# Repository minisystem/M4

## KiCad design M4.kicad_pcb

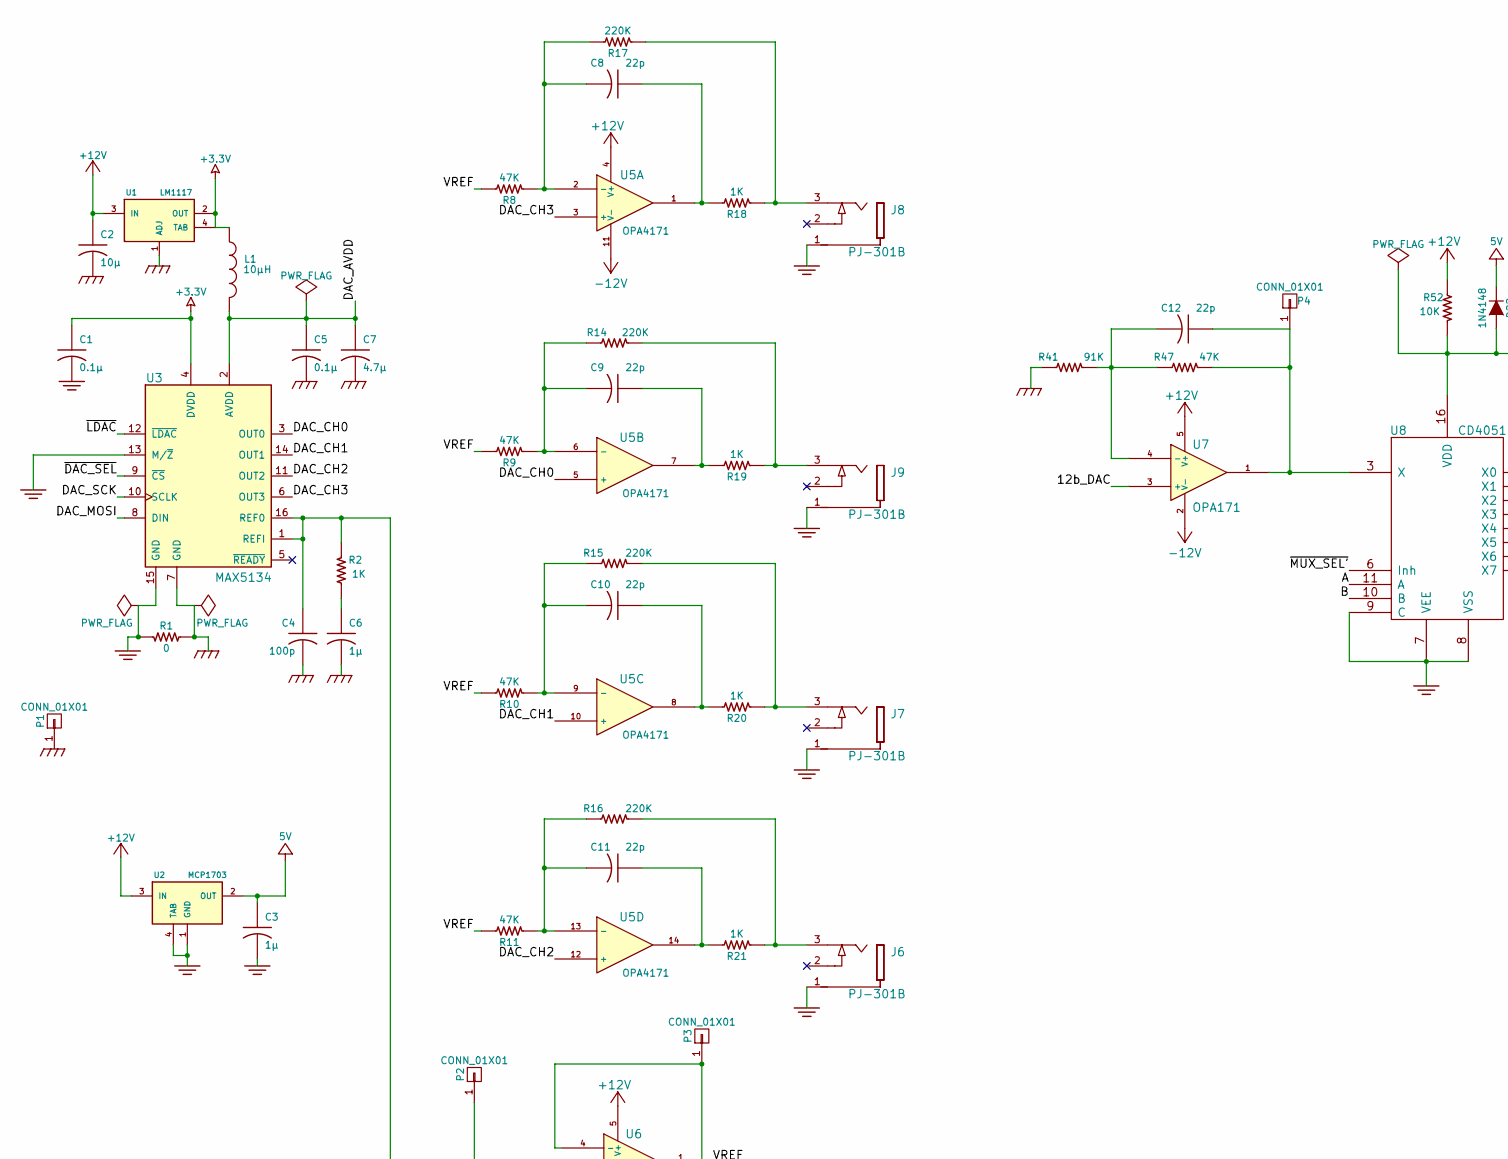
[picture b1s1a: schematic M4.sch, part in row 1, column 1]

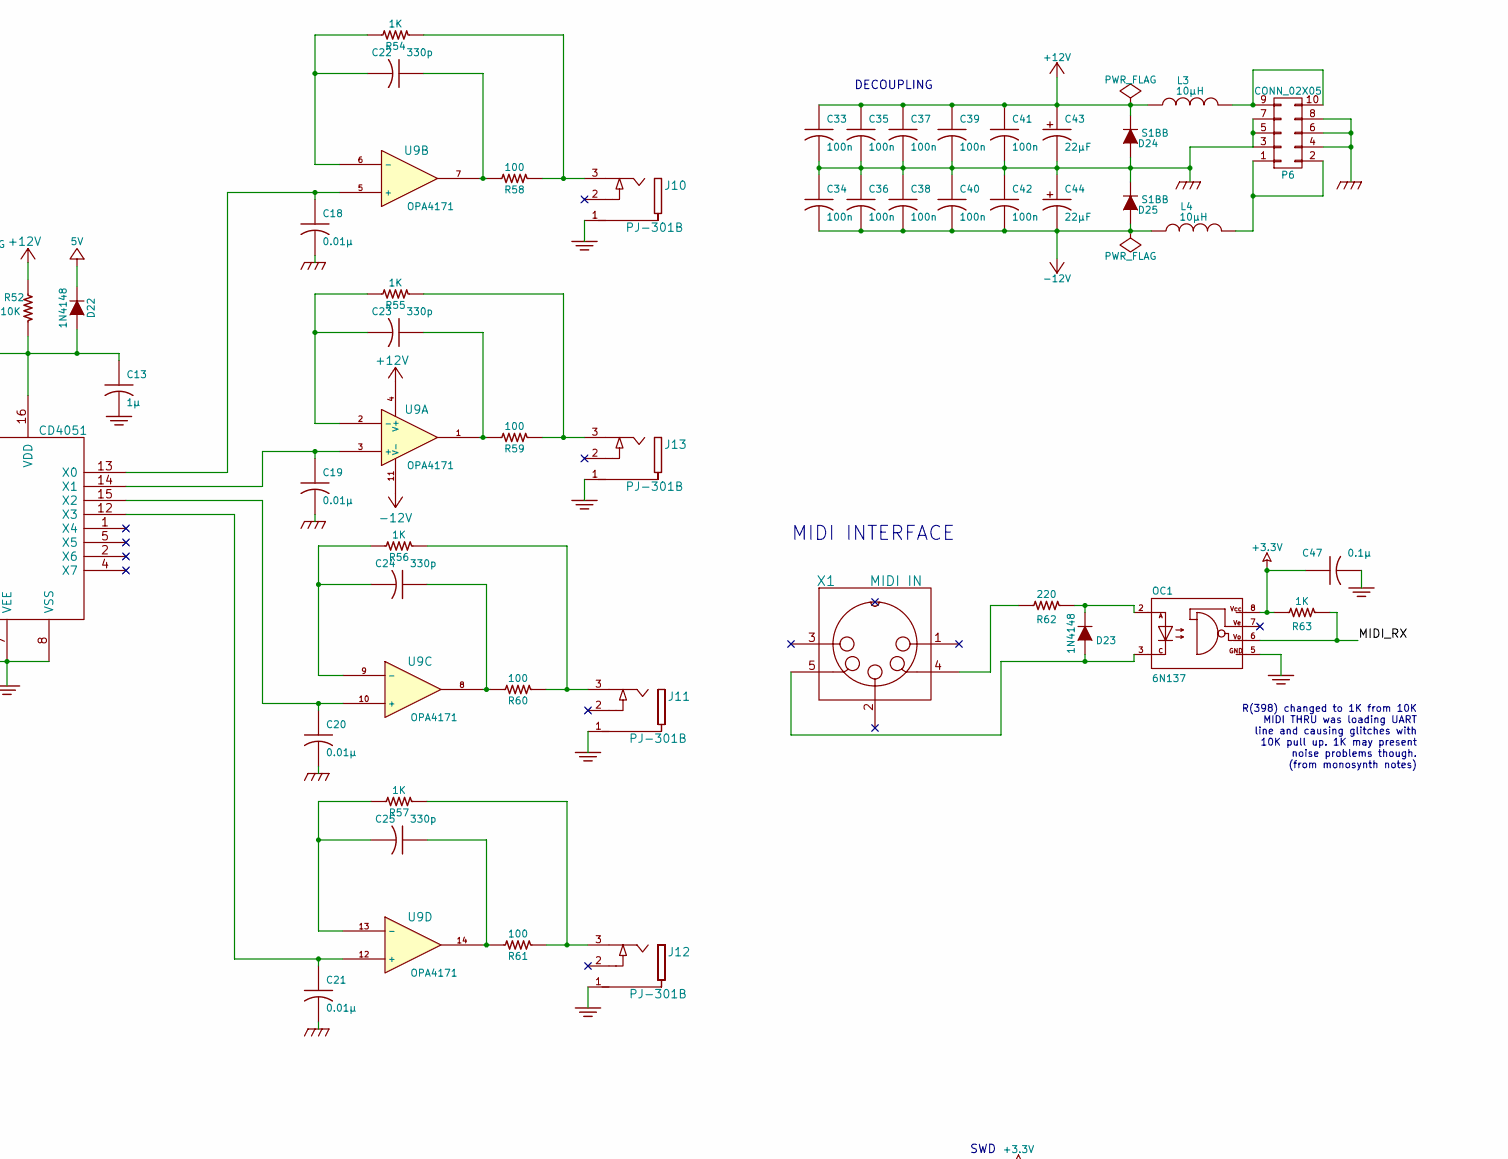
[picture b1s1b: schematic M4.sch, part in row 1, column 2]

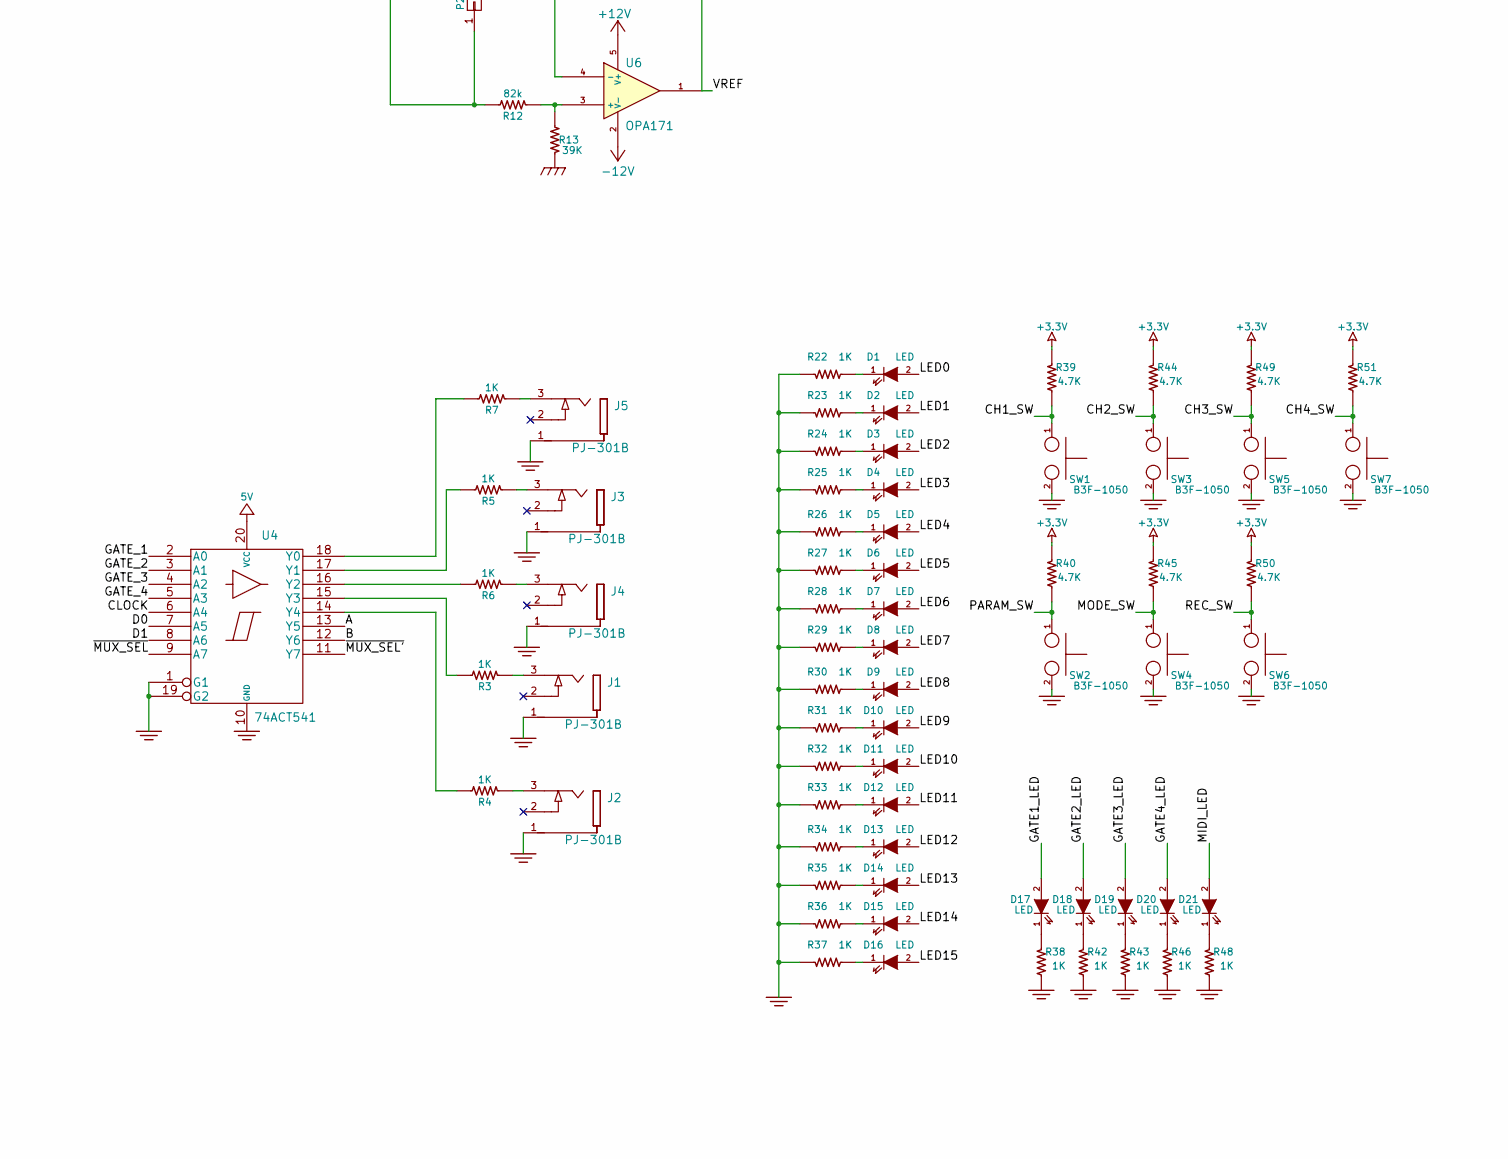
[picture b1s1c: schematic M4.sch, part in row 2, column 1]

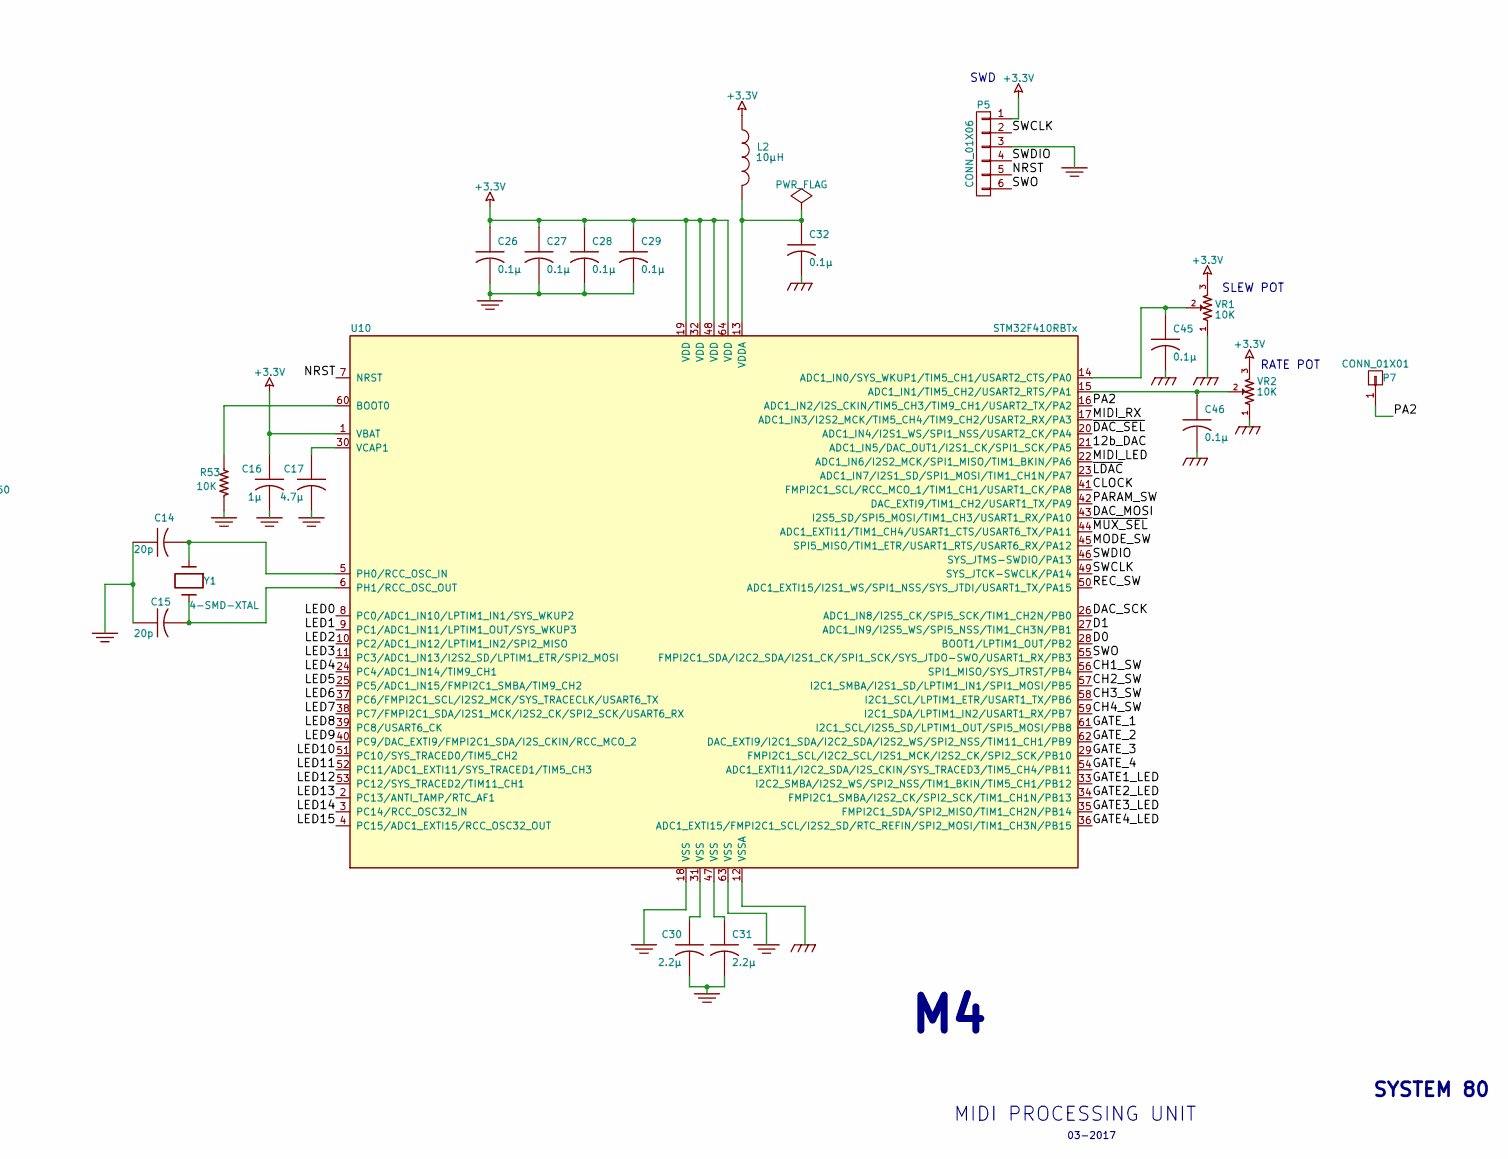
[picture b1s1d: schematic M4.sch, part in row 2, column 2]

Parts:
C1, C5, C26, C27, C28, C29, C32, C45, C46: 0.1μ; SM0603-C-JRL
C2: 10μ; SM0805-HAND
C3, C6, C13, C16: 1μ; SM0603-C-JRL
C4: 100p; SM0603-C-JRL
C7: 4.7μ; SM0805-HAND
C8, C9, C10, C11, C12: 22p; SM0603-C-JRL
C14, C15: 20p; SM0603-C-JRL
C17: 4.7μ; SM0603-C-JRL
C18, C19, C20, C21: 0.01μ; SM0603-C-JRL
C22, C23, C24, C25: 330p; SM0603-C-JRL
C30, C31: 2.2μ; SM0603-C-JRL
C33, C34, C35, C36, C37, C38, C39, C40, C41, C42: 100n; SM0603-C-JRL
C43, C44: 22μF; jrl_c_elec_5x5.3; Part Number UWJ1E100MCL1GB
C47: 0.1µ; SM0603-C-JRL
D1, D2, D3, D4, D5, D6, D7, D8, D9, D10, D11, D12, D13, D14, D15, D16, D17, D18, D19, D20, D21: LED; 1.8MM-LED-TLUG240
D22, D23: 1N4148; SOD323-C1A2
D24, D25: S1BB; SMB-1C2A
J1, J2, J3, J4, J5, J6, J7, J8, J9, J10, J11, J12, J13: PJ-301B; PJ-301B-JACK-SLOTS
L1, L2, L3, L4: 10μH; SM0603-R-JRL
OC1: 6N137; 8-SMD
P1: CONN_01X01; TEST_POINT_LOOP_4592
P2, P3, P4, P7: CONN_01X01; TEST_POINT_SMALL
P5: CONN_01X06; Pin_Header_Straight_1x06_Pitch2.54mm
P6: CONN_02X05; Pin_Header_Straight_2x05_Pitch2.54mm
R1: 0; SM0603-R-JRL
R2, R3, R4, R5, R6, R7, R18, R19, R20, R21, R22, R23, R24, R25, R26, R27, R28, R29, R30, R31, R32, R33, R34, R35, R36, R37, R38, R42, R43, R46, R48, R54, R55, R56, R57, R63: 1K; SM0603-R-JRL
R8, R9, R10, R11, R47: 47K; SM0603-R-JRL
R12: 82k; SM0603-R-JRL
R13: 39K; SM0603-R-JRL
R14, R15, R16, R17: 220K; SM0603-R-JRL
R39, R40, R44, R45, R49, R50, R51: 4.7K; SM0603-R-JRL
R41: 91K; SM0603-R-JRL
R52, R53: 10K; SM0603-R-JRL
R58, R59, R60, R61: 100; SM0603-R-JRL
R62: 220; SM0603-R-JRL
SW1, SW2, SW3, SW4, SW5, SW6, SW7: B3F-1050; B3F-1050-OMRON
U1: LM1117; SOT-223
U2: MCP1703; SOT-223
U3: MAX5134; TSSOP-16_4.4x5mm_Pitch0.65mm
U4: 74ACT541; TSSOP-20_4.4x6.5mm_Pitch0.65mm
U5, U9: OPA4171; TSSOP-14_4.4x5mm_Pitch0.65mm
U6, U7: OPA171; SOT-23-5
U8: CD4051; TSSOP-16_4.4x5mm_Pitch0.65mm_jrl
U10: STM32F410RBTx; LQFP-64_10x10mm_Pitch0.5mm
VR1, VR2: 10K; RV16A-41-JRL
X1: MIDI IN; SD-50BV-5DIN
Y1: 4-SMD-XTAL

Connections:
+3V3: C1.1, C16.1, C26.1, C27.1, C28.1, C29.1, C47.1, L1.1, L2.1, OC1.8, P5.1, R39.1, R40.1, R44.1, R45.1, R49.1, R50.1, R51.1, R63.2, U1.2 (OUT), U1.4 (TAB), U3.4 (DVDD), U10.1 (VBAT), U10.19 (VDD), U10.32 (VDD), U10.48 (VDD), U10.64 (VDD), VR1.3, VR2.3
+5V: C3.1, D22.1 (K), U2.2 (OUT), U4.20 (VCC)
+12V: C2.1, C33.1, C35.1, C37.1, C39.1, C41.1, C43.1 (+), D24.1 (K), L3.1, R52.1, U1.3 (IN), U2.3 (IN), U5.4 (V+), U6.5 (V+), U7.5 (V+), U9.4 (V+)
-12V: C34.2, C36.2, C38.2, C40.2, C42.2, C44.2 (-), D25.2 (A), L4.1, U5.11 (V-), U6.2 (V-), U7.2 (V-), U9.11 (V-)
/12b_DAC: U7.3 (+), U10.21 (ADC1_IN5/DAC_OUT1/I2S1_CK/SPI1_SCK/PA5)
/A: U4.13 (Y5), U8.11 (A)
/B: U4.12 (Y6), U8.10 (B)
/CH1_SW: R39.2, SW1.1, U10.56 (SPI1_MISO/SYS_JTRST/PB4)
/CH2_SW: R44.2, SW3.1, U10.57 (I2C1_SMBA/I2S1_SD/LPTIM1_IN1/SPI1_MOSI/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)
/CH3_SW: R49.2, SW5.1, U10.58 (I2C1_SCL/LPTIM1_ETR/USART1_TX/PB6)
/CH4_SW: R51.2, SW7.1, U10.59 (I2C1_SDA/LPTIM1_IN2/USART1_RX/PB7)
/CLOCK: U4.6 (A4), U10.41 (FMPI2C1_SCL/RCC_MCO_1/TIM1_CH1/USART1_C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)
/D0: U4.7 (A5), U10.28 (BOOT1/LPTIM1_OUT/PB2)
/D1: U4.8 (A6), U10.27 (ADC1_IN9/I2S5_WS/SPI5_NSS/TIM1_CH3N/PB1)
/DAC_AVDD: C5.1, C7.1, L1.2, U3.2 (AVDD)
/DAC_CH0: U3.3 (OUT0), U5.5 (+)
/DAC_CH1: U3.14 (OUT1), U5.10 (+)
/DAC_CH2: U3.11 (OUT2), U5.12 (+)
/DAC_CH3: U3.6 (OUT3), U5.3 (+)
/DAC_MOSI: U3.8 (DIN), U10.43 (I2S5_SD/SPI5_MOSI/TIM1_CH3/USART1_RX/PA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)
/DAC_SCK: U3.10 (SCLK), U10.26 (ADC1_IN8/I2S5_CK/SPI5_SCK/TIM1_CH2N/PB0)
/GATE1_LED: D17.2 (A), U10.33 (I2C2_SMBA/I2S2_WS/SPI2_NSS/TIM1_BKIN/TI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)
/GATE2_LED: D18.2 (A), U10.34 (FMPI2C1_SMBA/I2S2_CK/SPI2_SCK/TIM1_CH1N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)
/GATE3_LED: D19.2 (A), U10.35 (FMPI2C1_SDA/SPI2_MISO/TIM1_CH2N/PB14)
/GATE4_LED: D20.2 (A), U10.36 (ADC1_EXTI15/FMPI2C1_SCL/I2S2_SD/RTC_REF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)
/GATE_1: U4.2 (A0), U10.61 (I2C1_SCL/I2S5_SD/LPTIM1_OUT/SPI5_MOSI/P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)
/GATE_2: U4.3 (A1), U10.62 (DAC_EXTI9/I2C1_SDA/I2C2_SDA/I2S2_WS/SPI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)
/GATE_3: U4.4 (A2), U10.29 (FMPI2C1_SCL/I2C2_SCL/I2S1_MCK/I2S2_CK/S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)
/GATE_4: U4.5 (A3), U10.54 (ADC1_EXTI11/I2C2_SDA/I2S_CKIN/SYS_TRACE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)
/LED0: D1.2 (A), U10.8 (PC0/ADC1_IN10/LPTIM1_IN1/SYS_WKUP2)
/LED1: D2.2 (A), U10.9 (PC1/ADC1_IN11/LPTIM1_OUT/SYS_WKUP3)
/LED2: D3.2 (A), U10.10 (PC2/ADC1_IN12/LPTIM1_IN2/SPI2_MISO)
/LED3: D4.2 (A), U10.11 (PC3/ADC1_IN13/I2S2_SD/LPTIM1_ETR/SPI2_M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)
/LED4: D5.2 (A), U10.24 (PC4/ADC1_IN14/TIM9_CH1)
/LED5: D6.2 (A), U10.25 (PC5/ADC1_IN15/FMPI2C1_SMBA/TIM9_CH2)
/LED6: D7.2 (A), U10.37 (PC6/FMPI2C1_SCL/I2S2_MCK/SYS_TRACECLK/U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)
/LED7: D8.2 (A), U10.38 (PC7/FMPI2C1_SDA/I2S1_MCK/I2S2_CK/SPI2_S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)
/LED8: D9.2 (A), U10.39 (PC8/USART6_CK)
/LED9: D10.2 (A), U10.40 (PC9/DAC_EXTI9/FMPI2C1_SDA/I2S_CKIN/RCC_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)
/LED10: D11.2 (A), U10.51 (PC10/SYS_TRACED0/TIM5_CH2)
/LED11: D12.2 (A), U10.52 (PC11/ADC1_EXTI11/SYS_TRACED1/TIM5_CH3)
/LED12: D13.2 (A), U10.53 (PC12/SYS_TRACED2/TIM11_CH1)
/LED13: D14.2 (A), U10.2 (PC13/ANTI_TAMP/RTC_AF1)
/LED14: D15.2 (A), U10.3 (PC14/RCC_OSC32_IN)
/LED15: D16.2 (A), U10.4 (PC15/ADC1_EXTI15/RCC_OSC32_OUT)
/MIDI_LED: D21.2 (A), U10.22 (ADC1_IN6/I2S2_MCK/SPI1_MISO/TIM1_BKIN/P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)
/MIDI_RX: OC1.6, R63.1, U10.17 (ADC1_IN3/I2S2_MCK/TIM5_CH4/TIM9_CH2/USA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)
/MODE_SW: R45.2, SW4.1, U10.45 (SPI5_MISO/TIM1_ETR/USART1_RTS/USART6_RX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)
/NRST: P5.5, U10.7 (NRST)
/PA2: P7.1, U10.16 (ADC1_IN2/I2S_CKIN/TIM5_CH3/TIM9_CH1/USA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)
/PARAM_SW: R40.2, SW2.1, U10.42 (DAC_EXTI9/TIM1_CH2/USART1_TX/PA9)
/REC_SW: R50.2, SW6.1, U10.50 (ADC1_EXTI15/I2S1_WS/SPI1_NSS/SYS_JTDI/U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)
/SWCLK: P5.2, U10.49 (SYS_JTCK-SWCLK/PA14)
/SWDIO: P5.4, U10.46 (SYS_JTMS-SWDIO/PA13)
/SWO: P5.6, U10.55 (FMPI2C1_SDA/I2C2_SDA/I2S1_CK/SPI1_SCK/S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)
/VREF: P3.1, R8.2, R9.2, R10.2, R11.2, U6.1, U6.4 (-)
/~DAC_SEL: U3.9 (~CS~), U10.20 (ADC1_IN4/I2S1_WS/SPI1_NSS/USART2_CK/PA4)
/~LDAC: U3.12 (~LDAC~), U10.23 (ADC1_IN7/I2S1_SD/SPI1_MOSI/TIM1_CH1N/PA7)
/~MUX_SEL: U4.9 (A7), U10.44 (ADC1_EXTI11/TIM1_CH4/USART1_CTS/USART6_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)
/~MUX_SEL': U4.11 (Y7), U8.6 (Inh)
unnamed: C4.1, P2.1, R2.1, R12.2, U3.1 (REFI), U3.16 (REF0)
unnamed: C6.1, R2.2
unnamed: C8.1, R18.2, U5.1
unnamed: C8.2, R8.1, R17.2, U5.2 (-)
unnamed: C9.1, R19.2, U5.7
unnamed: C9.2, R9.1, R14.2, U5.6 (-)
unnamed: C10.1, R20.2, U5.8
unnamed: C10.2, R10.1, R15.2, U5.9 (-)
unnamed: C11.1, R21.2, U5.14
unnamed: C11.2, R11.1, R16.2, U5.13 (-)
unnamed: C12.1, P4.1, R47.1, U7.1, U8.3 (X)
unnamed: C12.2, R41.1, R47.2, U7.4 (-)
unnamed: C13.1, D22.2 (A), R52.2, U8.16 (VDD)
unnamed: C14.2, U10.5 (PH0/RCC_OSC_IN), Y1.1
unnamed: C15.2, U10.6 (PH1/RCC_OSC_OUT), Y1.3
unnamed: C17.1, U10.30 (VCAP1)
unnamed: C18.1, U8.13 (X0), U9.5 (+)
unnamed: C19.1, U8.14 (X1), U9.3 (+)
unnamed: C20.1, U8.15 (X2), U9.10 (+)
unnamed: C21.1, U8.12 (X3), U9.12 (+)
unnamed: C22.1, R58.2, U9.7
unnamed: C22.2, R54.2, U9.6 (-)
unnamed: C23.1, R59.2, U9.1
unnamed: C23.2, R55.2, U9.2 (-)
unnamed: C24.1, R60.2, U9.8
unnamed: C24.2, R56.2, U9.9 (-)
unnamed: C25.1, R61.2, U9.14
unnamed: C25.2, R57.2, U9.13 (-)
unnamed: C30.1, U10.31 (VSS)
unnamed: C31.1, U10.47 (VSS)
unnamed: C32.1, L2.2, U10.13 (VDDA)
unnamed: C45.1, U10.14 (ADC1_IN0/SYS_WKUP1/TIM5_CH1/USART2_CTS/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), VR1.2
unnamed: C46.1, U10.15 (ADC1_IN1/TIM5_CH2/USART2_RTS/PA1), VR2.2
unnamed: D1.1 (K), R22.2
unnamed: D2.1 (K), R23.2
unnamed: D3.1 (K), R24.2
unnamed: D4.1 (K), R25.2
unnamed: D5.1 (K), R26.2
unnamed: D6.1 (K), R27.2
unnamed: D7.1 (K), R28.2
unnamed: D8.1 (K), R29.2
unnamed: D9.1 (K), R30.2
unnamed: D10.1 (K), R31.2
unnamed: D11.1 (K), R32.2
unnamed: D12.1 (K), R33.2
unnamed: D13.1 (K), R34.2
unnamed: D14.1 (K), R35.2
unnamed: D15.1 (K), R36.2
unnamed: D16.1 (K), R37.2
unnamed: D17.1 (K), R38.1
unnamed: D18.1 (K), R42.1
unnamed: D19.1 (K), R43.1
unnamed: D20.1 (K), R46.1
unnamed: D21.1 (K), R48.1
unnamed: D23.1 (K), OC1.2, R62.1
unnamed: D23.2 (A), OC1.3, X1.5
unnamed: J1.3, R3.1
unnamed: J2.3, R4.1
unnamed: J3.3, R5.1
unnamed: J4.3, R6.1
unnamed: J5.3, R7.1
unnamed: J6.3, R16.1, R21.1
unnamed: J7.3, R15.1, R20.1
unnamed: J8.3, R17.1, R18.1
unnamed: J9.3, R14.1, R19.1
unnamed: J10.3, R54.1, R58.1
unnamed: J11.3, R56.1, R60.1
unnamed: J12.3, R57.1, R61.1
unnamed: J13.3, R55.1, R59.1
unnamed: L3.2, P6.9, P6.10
unnamed: L4.2, P6.1, P6.2
unnamed: R3.2, U4.15 (Y3)
unnamed: R4.2, U4.14 (Y4)
unnamed: R5.2, U4.17 (Y1)
unnamed: R6.2, U4.16 (Y2)
unnamed: R7.2, U4.18 (Y0)
unnamed: R12.1, R13.2, U6.3 (+)
unnamed: R53.1, U10.60 (BOOT0)
unnamed: R62.2, X1.4

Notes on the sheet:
DECOUPLING
MIDI INTERFACE
R(398) changed to 1K from 10K MIDI THRU was loading UART line and causing glitches with 10K pull up. 1K may present noise problems though. (from monosynth notes)
SWD
SLEW POT
RATE POT
SYSTEM 80
03-2017
MIDI PROCESSING UNIT

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
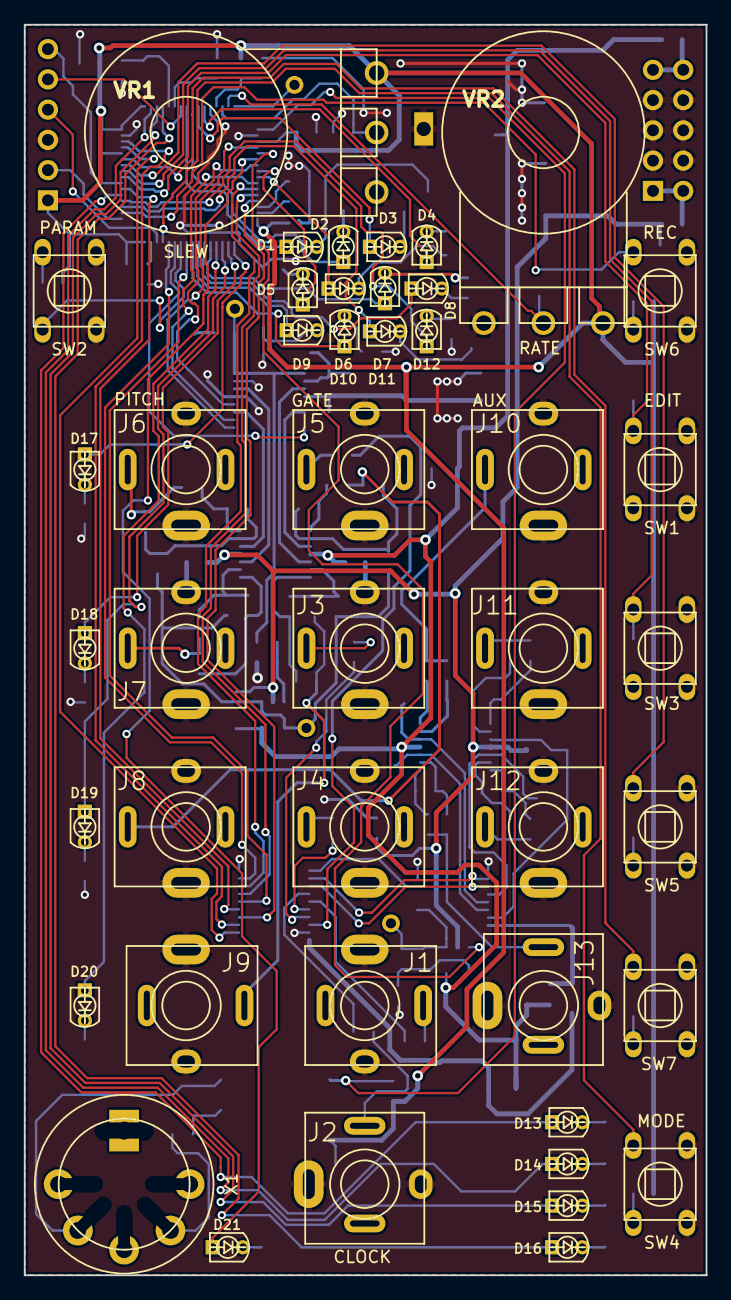
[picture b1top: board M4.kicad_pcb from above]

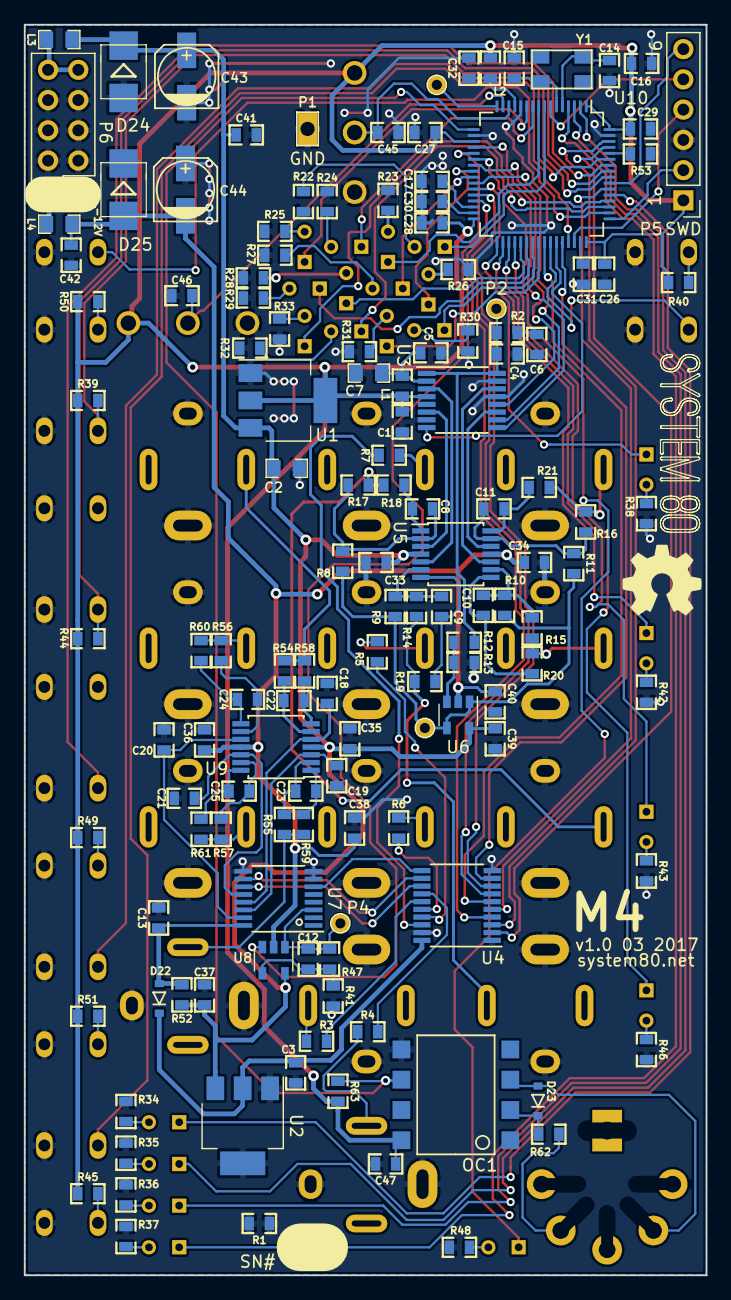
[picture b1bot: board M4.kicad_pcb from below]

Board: 2 copper layers, 57.2 x 105.0 mm, 181 parts (137 on the bottom side), 140 nets.

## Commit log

2017-03-14 added panel folder and artwork
2017-03-14 almost finished schematic capture
2017-03-14 updated panel svg for Inkscape 0.91, schematic annotated and ERC complete
2017-03-15 placed pots/jacks/switches on PCB. not a lot of room left for ICs
2017-03-15 routing.
2017-03-16 routing..
2017-03-16 routing...
2017-03-16 routing....
2017-03-17 basically routed. need to delete excess decoupling caps and decide about whether external sw pull up resistors are necessary - probably not and need to be deleted
2017-03-17 routed.
2017-03-18 updated some 3D part assignments
2017-03-18 changed LED models to TLUGX240
2017-03-18 tidied up front silkscreen
2017-03-19 routing and silkscreen done. just need to check everything and then ready to order
2017-03-21 going through final checking stages, then will be ready to order PCB
2017-03-21 generated gerbers, ready to order
2017-03-22 PCBs ordered
